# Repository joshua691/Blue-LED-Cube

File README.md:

# 4×4×4 Blue LED Cube

A 4×4×4 LED cube controlled by an Arduino using transistors and multiplexing, achieving flicker-free animation at 250 Hz with a 25% refresh rate. This project demonstrates circuit design, embedded programming, and PCB layout skills using KiCad.

**Status: Completed**

## Overview
This project includes:
- Circuit schematic and PCB layout designed in KiCad
- Transistor-based control logic for efficient multiplexing
- Breadboard prototype and final soldered cube
- Modular design enabling microcontroller swaps and future feature expansion

## Features
- Flicker-free LED animation at **250 Hz**
- Power-efficient design using transistors and multiplexing
- Modular perfboard design for easy maintenance and upgrades
- Interactive features using ESP32 microcontroller

## Tools & Technologies
- **Hardware:** Arduino, 64x LEDs, 16x 470 ohm resistors, 4x transistors, 2x 74HC595 shift registers, perfboard
- **Software:** KiCad, Arduino IDE, C++
- **Other:** Breadboard prototyping, soldering

## Project Structure
- **Columns:** Each of the 16 LED columns shares a common anode, each connected to a pin on a 74HC595 shift register.
- **Layers:** Each of the 4 layers shares a common cathode, controlled by transistors to select which layer is grounded.
- **Control:** Arduino pins drive the shift registers and transistors to create multiplexed animation.

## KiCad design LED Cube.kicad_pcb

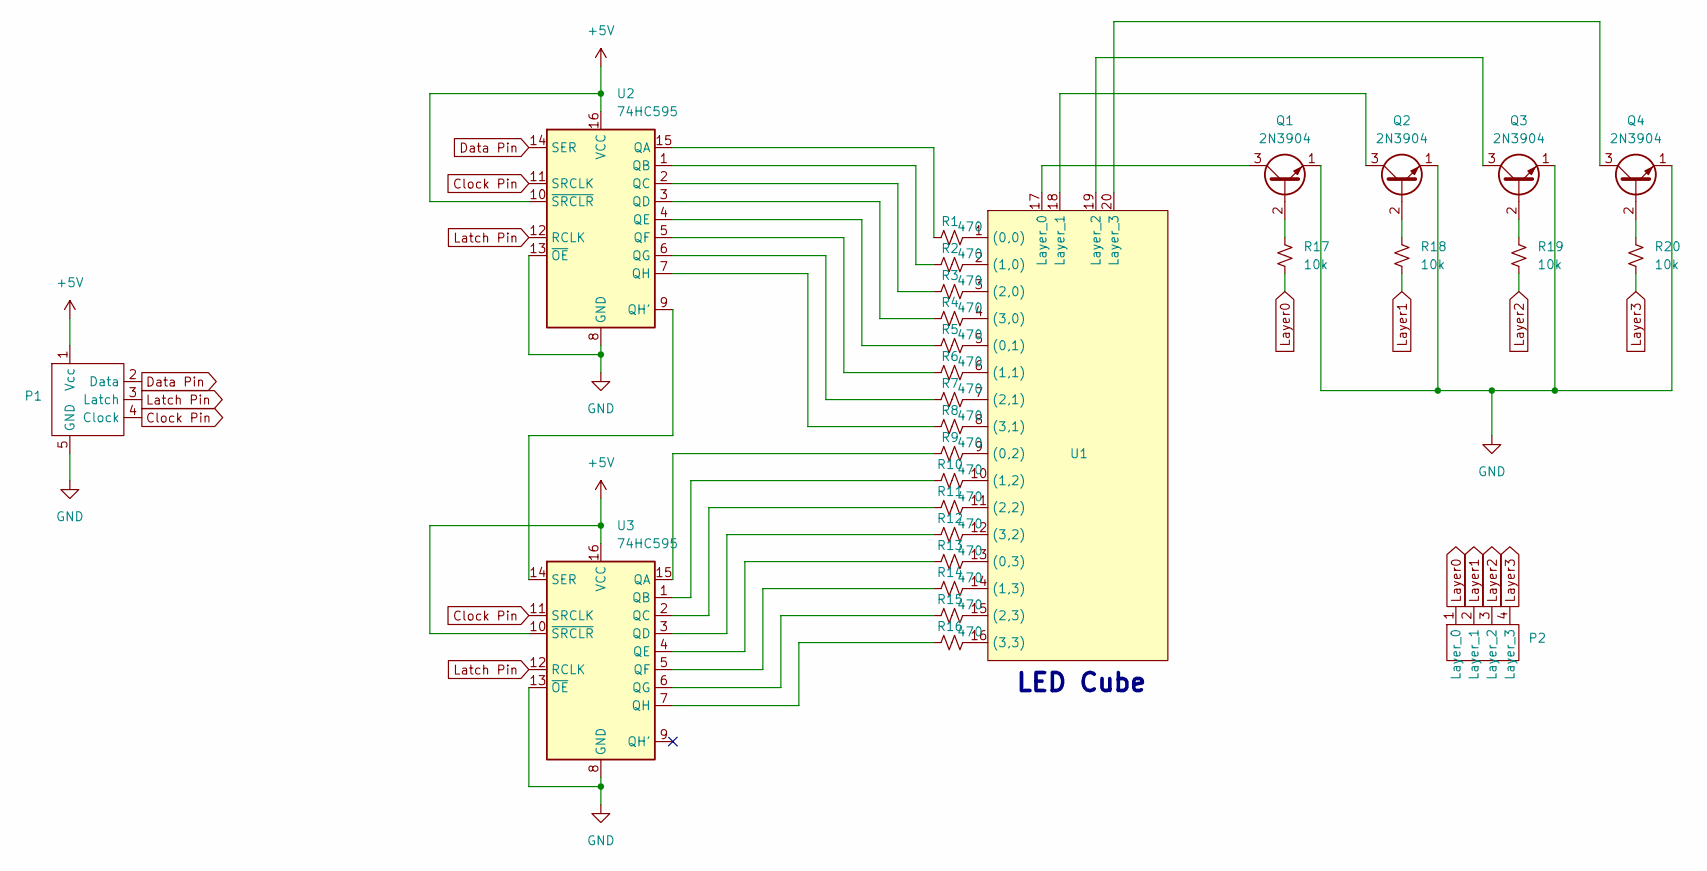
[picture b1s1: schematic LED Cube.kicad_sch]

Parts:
P1: Input_Pin_Connections
P2: Layer_Pin_Connections
Q1, Q2, Q3, Q4: 2N3904; TO-92_Inline
R1, R2, R3, R4, R5, R6, R7, R8, R9, R10, R11, R12, R13, R14, R15, R16: 470; R_Axial_DIN0207_L6.3mm_D2.5mm_P7.62mm_Horizontal
R17, R18, R19, R20: 10k; R_Axial_DIN0207_L6.3mm_D2.5mm_P7.62mm_Horizontal
U1: LED_Cube
U2, U3: 74HC595; 74HC595 Shift Register

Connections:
+5V: P1.1 (Vcc), U2.10 (~SRCLR), U2.16 (VCC), U3.10 (~SRCLR), U3.16 (VCC)
Clock Pin: P1.4 (Clock), U2.11 (SRCLK), U3.11 (SRCLK)
Data Pin: P1.2 (Data), U2.14 (SER)
GND: P1.5 (GND), Q1.1 (E), Q2.1 (E), Q3.1 (E), Q4.1 (E), U2.8 (GND), U2.13 (~OE), U3.8 (GND), U3.13 (~OE)
Latch Pin: P1.3 (Latch), U2.12 (RCLK), U3.12 (RCLK)
Layer0: P2.1 (Layer_0), R17.2
Layer1: P2.2 (Layer_1), R18.2
Layer2: P2.3 (Layer_2), R19.2
Layer3: P2.4 (Layer_3), R20.2
unnamed: Q1.2 (B), R17.1
unnamed: Q1.3 (C), U1.17 (Layer_0)
unnamed: Q2.2 (B), R18.1
unnamed: Q2.3 (C), U1.18 (Layer_1)
unnamed: Q3.2 (B), R19.1
unnamed: Q3.3 (C), U1.19 (Layer_2)
unnamed: Q4.2 (B), R20.1
unnamed: Q4.3 (C), U1.20 (Layer_3)
unnamed: R1.2, U1.1 ((0,0))
unnamed: R5.2, U1.5 ((0,1))
unnamed: R9.2, U1.9 ((0,2))
unnamed: R13.2, U1.13 ((0,3))
unnamed: R2.2, U1.2 ((1,0))
unnamed: R6.2, U1.6 ((1,1))
unnamed: R10.2, U1.10 ((1,2))
unnamed: R14.2, U1.14 ((1,3))
unnamed: R3.2, U1.3 ((2,0))
unnamed: R7.2, U1.7 ((2,1))
unnamed: R11.2, U1.11 ((2,2))
unnamed: R15.2, U1.15 ((2,3))
unnamed: R4.2, U1.4 ((3,0))
unnamed: R8.2, U1.8 ((3,1))
unnamed: R12.2, U1.12 ((3,2))
unnamed: R16.2, U1.16 ((3,3))
unnamed: R1.1, U2.15 (QA)
unnamed: R2.1, U2.1 (QB)
unnamed: R3.1, U2.2 (QC)
unnamed: R4.1, U2.3 (QD)
unnamed: R5.1, U2.4 (QE)
unnamed: R6.1, U2.5 (QF)
unnamed: R7.1, U2.6 (QG)
unnamed: U2.9 (QH'), U3.14 (SER)
unnamed: R8.1, U2.7 (QH)
unnamed: R9.1, U3.15 (QA)
unnamed: R10.1, U3.1 (QB)
unnamed: R11.1, U3.2 (QC)
unnamed: R12.1, U3.3 (QD)
unnamed: R13.1, U3.4 (QE)
unnamed: R14.1, U3.5 (QF)
unnamed: R15.1, U3.6 (QG)
unnamed: R16.1, U3.7 (QH)

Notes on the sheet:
LED Cube

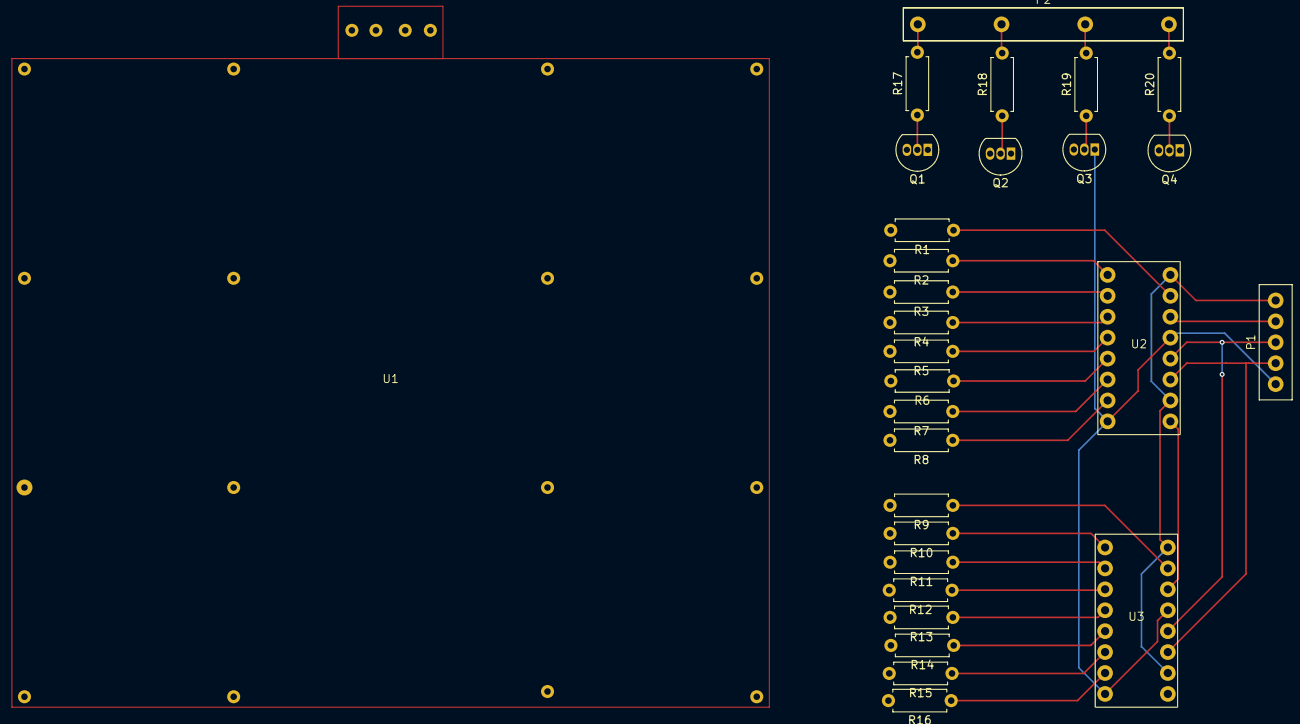
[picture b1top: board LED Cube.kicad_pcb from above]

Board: 2 copper layers, 29 parts (0 on the bottom side), 50 nets.

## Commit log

2025-09-23 Initial commit: KiCad files
2025-09-23 added kicad files to one folder
2025-09-23 adding schematic and PCB layout
2025-09-23 added schematics for top and side view
2025-09-23 added images and gifs
2025-09-23 Add files via upload
    added Arduino code
2025-09-23 added comments
2025-09-24 Added gif
2025-09-24 Remove gif
